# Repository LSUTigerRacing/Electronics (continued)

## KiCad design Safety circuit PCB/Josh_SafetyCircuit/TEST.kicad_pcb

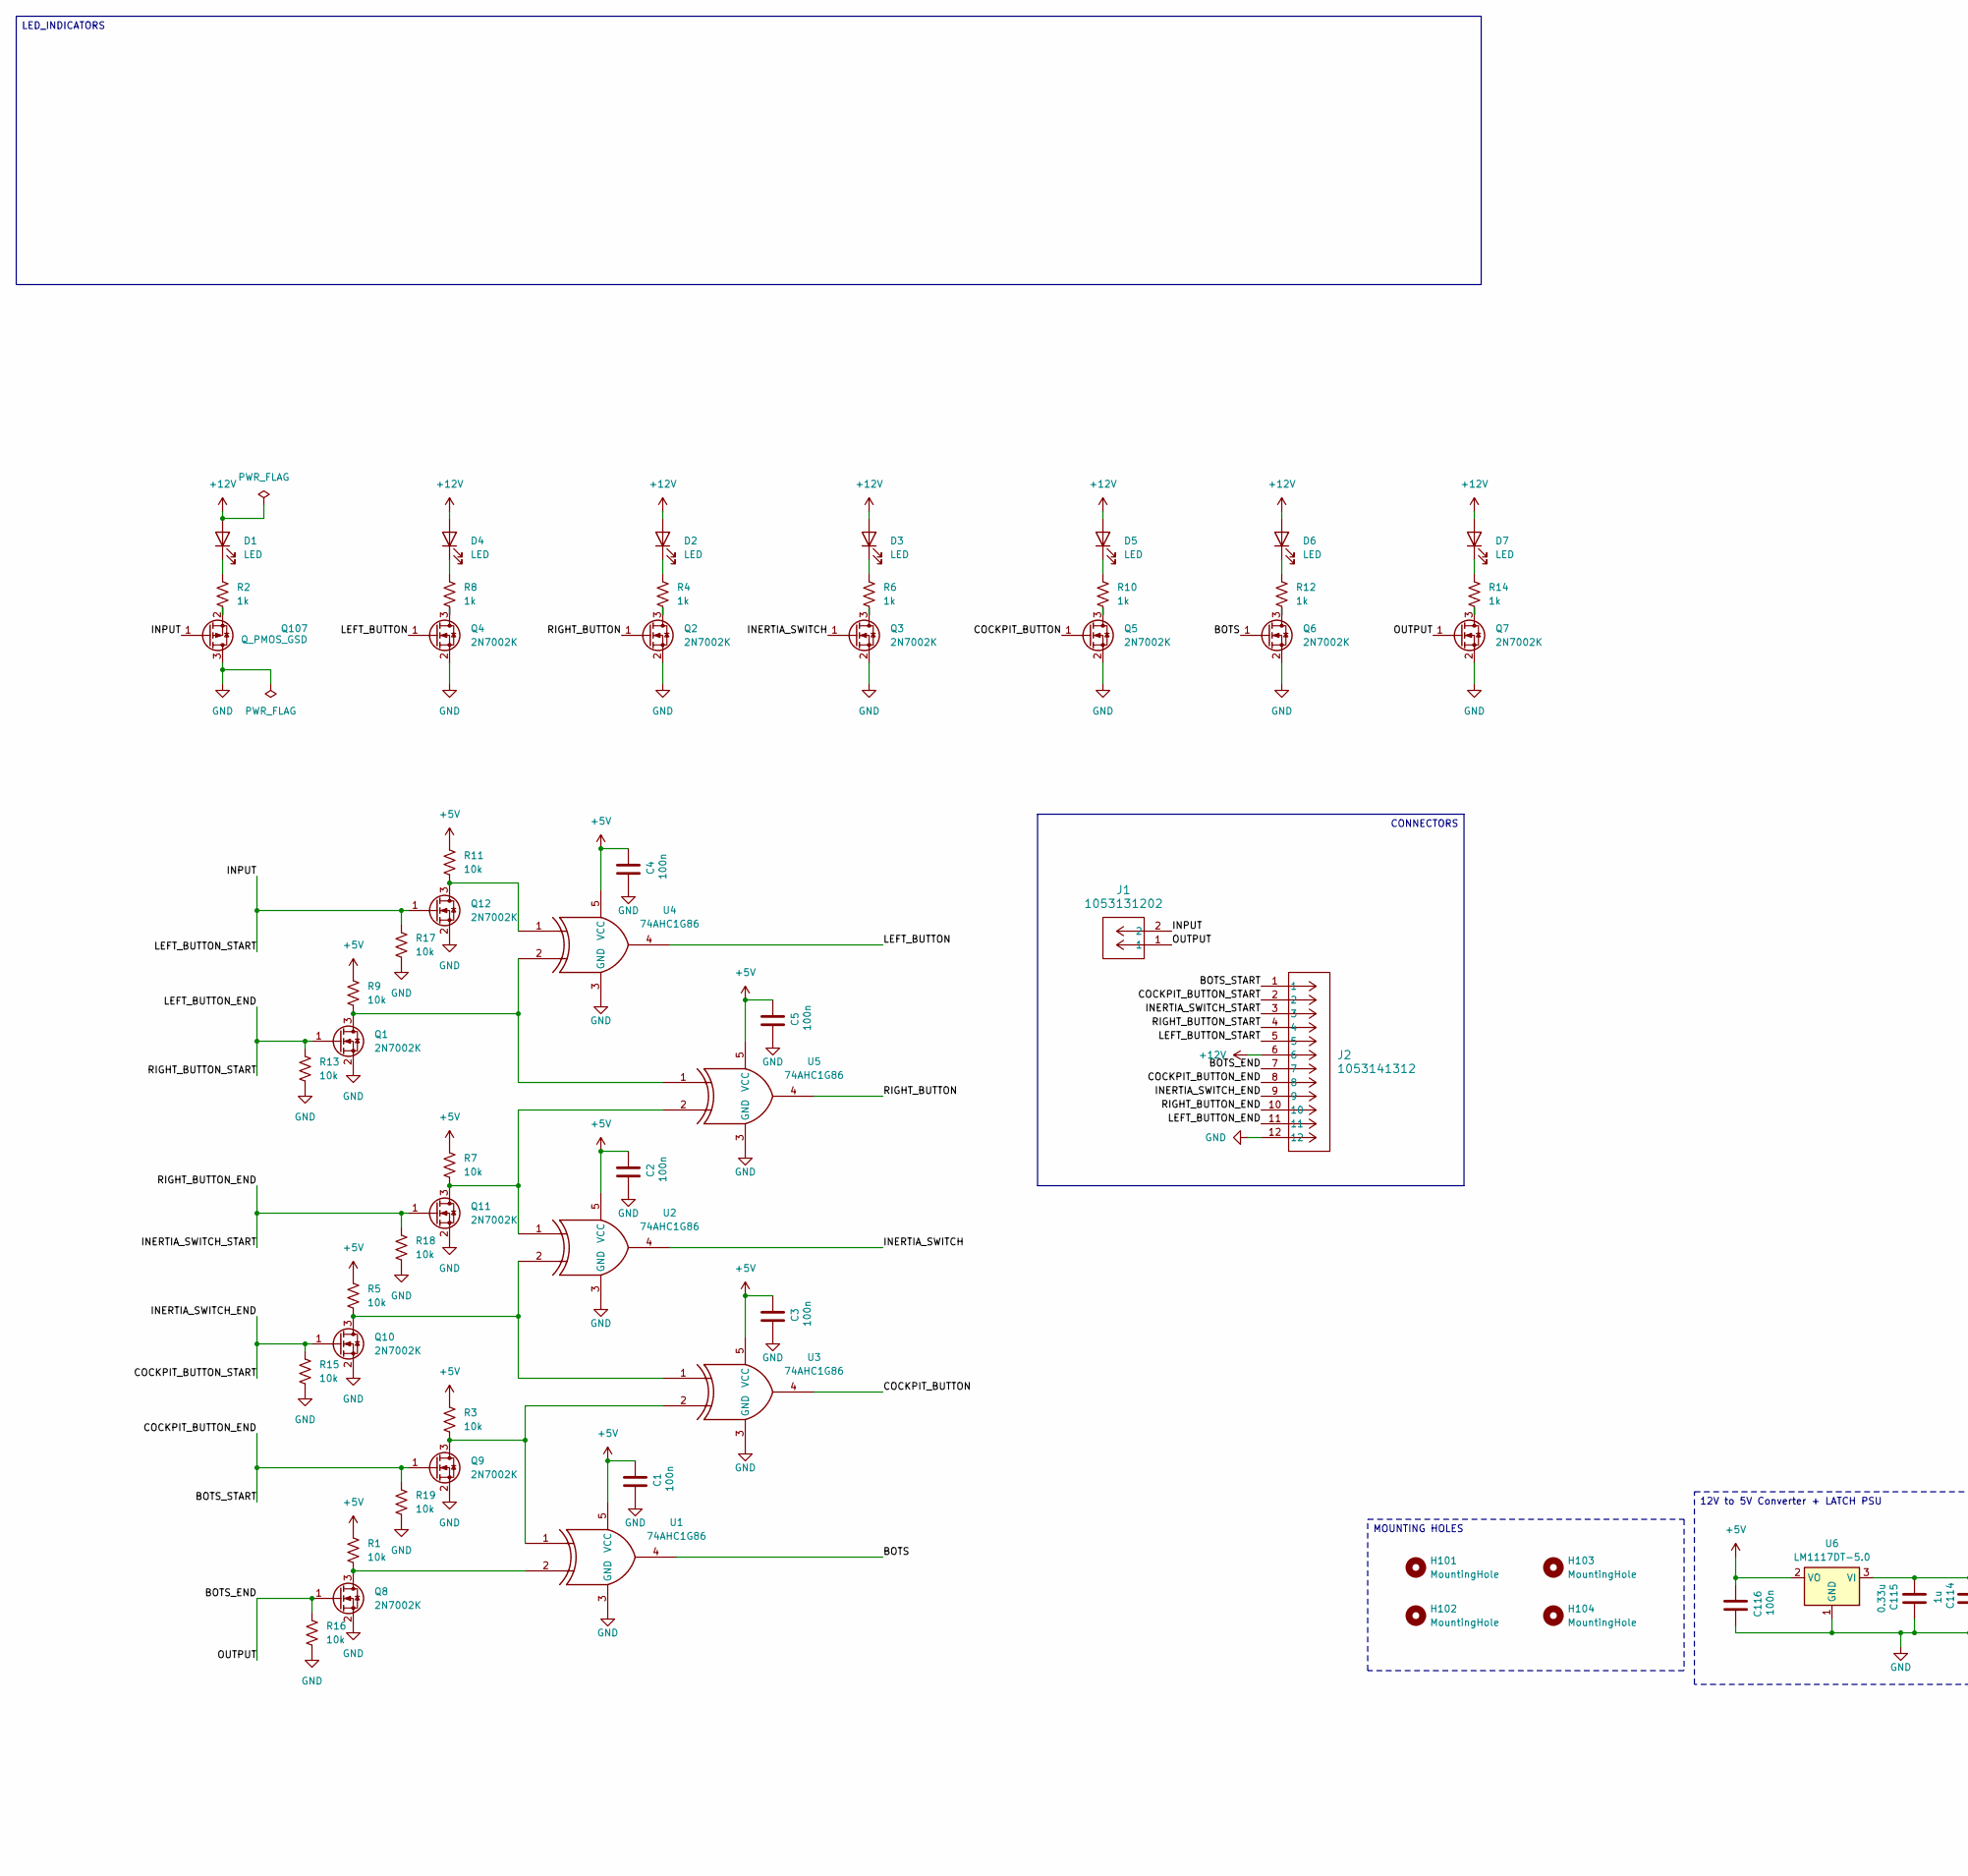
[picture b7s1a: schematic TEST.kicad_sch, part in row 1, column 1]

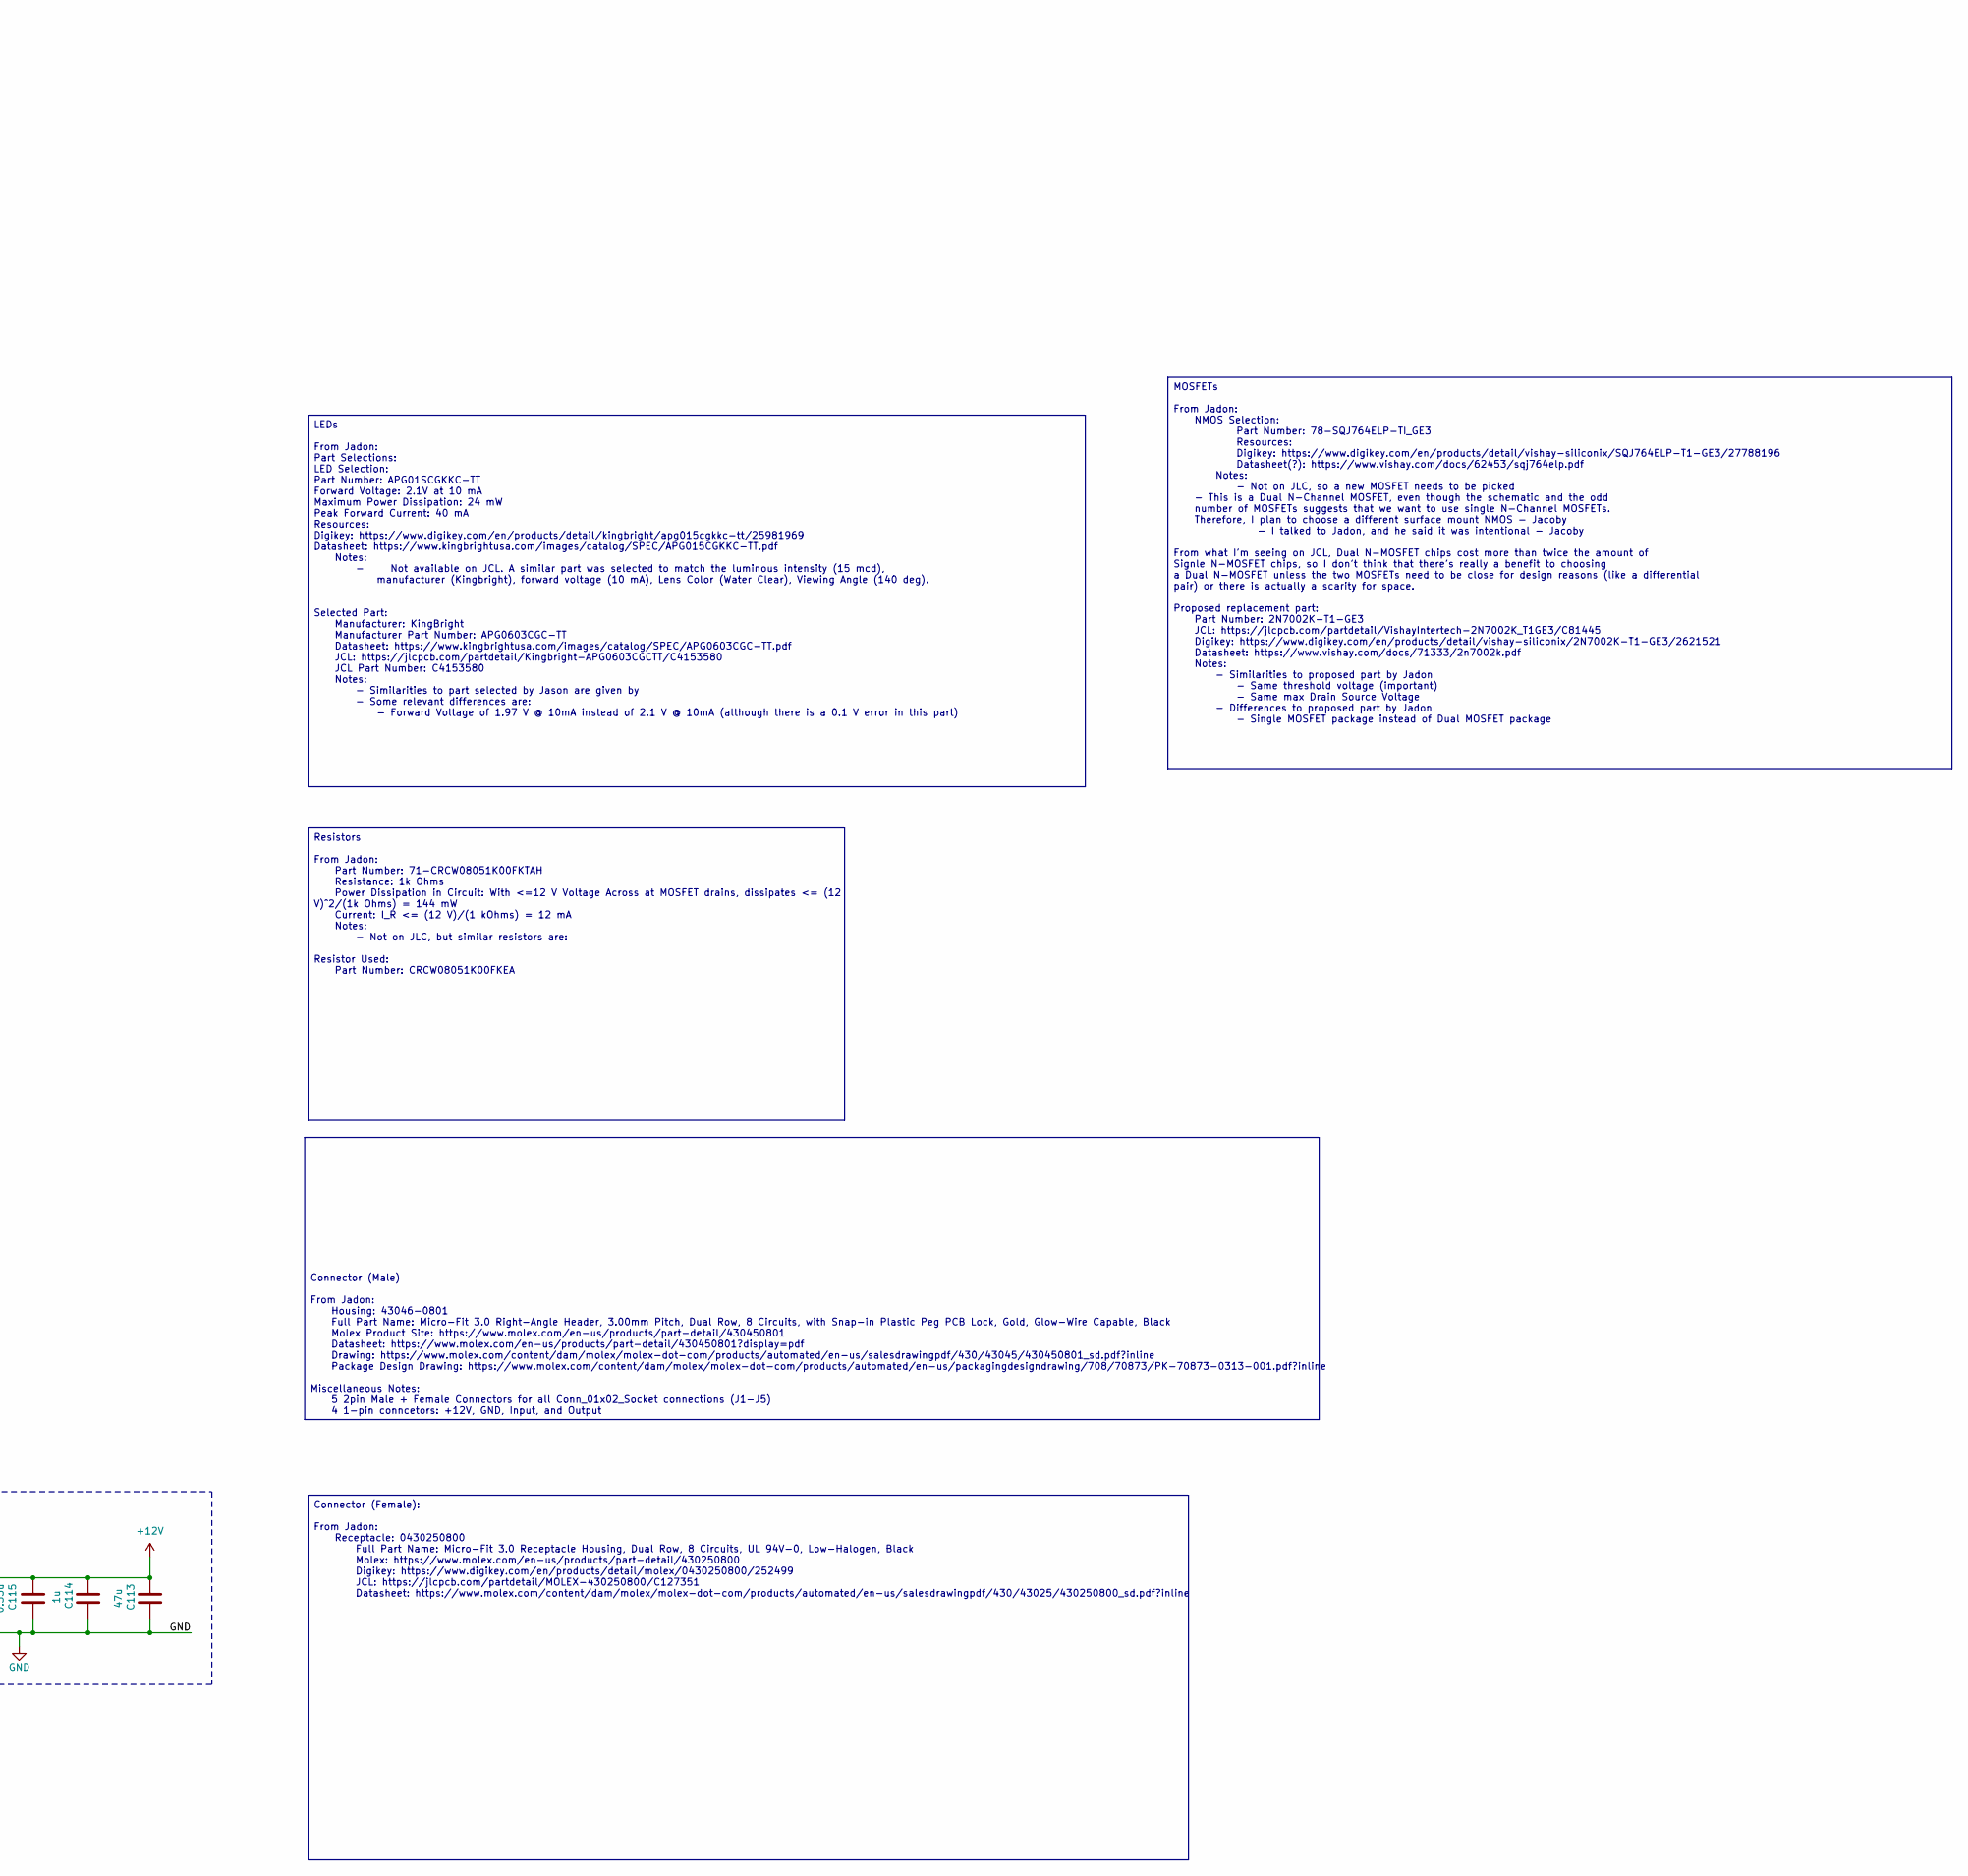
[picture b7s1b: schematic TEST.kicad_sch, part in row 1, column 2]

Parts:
C1, C2, C3, C4, C5, C116: 100n; C_0603_1608Metric_Pad1.08x0.95mm_HandSolder; JLC# C1591
C113: 47u; CP_Elec_6.3x5.4; JLC# C2836440
C114: 1u; C_0805_2012Metric_Pad1.18x1.45mm_HandSolder; JLC# C91186
C115: 0.33u; C_0603_1608Metric_Pad1.08x0.95mm_HandSolder; JLC# C282682
D1, D2, D3, D4, D5, D6, D7: LED; HL-PSC-1608U52GC-G4; MFR Part # PSC-1608U50GC-G4; JLC Part # C22371297
H101, H102, H103, H104: MountingHole; MountingHole_4.3mm_M4_DIN965_Pad_TopOnly
J1: 1053131202; CONN_SD-105313-100_02_MOL; MFR Part # 1053131202; JLC Part # C586242
J2: 1053141312; CONN_SD-105314-100_12_MOL; MFR Part # 1053141312; JLC Part # C17318123
Q1, Q2, Q3, Q4, Q5, Q6, Q7, Q8, Q9, Q10, Q11, Q12: 2N7002K; SOT-23; MFR Part # 2N7002K-T1-GE3; JLC Part # C81445
Q107: Q_PMOS_GSD; SOT-523; JLC# C96676
R1, R3, R5, R7, R9, R11, R13, R15, R16, R17, R18, R19: 10k; CRCW0805; MFR Part # CRCW08051K00FKEA; JLC Part # C844939
R2, R4, R6, R8, R10, R12, R14: 1k; CRCW0805; MFR Part # CRCW08051K00FKEA; JLC Part # C844939
U1, U2, U3, U4, U5: 74AHC1G86; SOT-23-5_HandSoldering
U6: LM1117DT-5.0; TO-252-3_TabPin2; JLC# C354068

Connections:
+5V: C1.2, C2.2, C3.2, C4.2, C5.2, C116.2, R1.1, R3.1, R5.1, R7.1, R9.1, R11.1, U1.5 (VCC), U2.5 (VCC), U3.5 (VCC), U4.5 (VCC), U5.5 (VCC), U6.2 (VO)
+12V: C113.1, C114.1, C115.1, D1.2 (A), D2.2 (A), D3.2 (A), D4.2 (A), D5.2 (A), D6.2 (A), D7.2 (A), J2.6, U6.3 (VI)
/BOTS: Q6.1 (G), U1.4
/BOTS_END: J1.1, J2.7, Q7.1 (G), Q8.1 (G), R16.1
/BOTS_START: J2.1, J2.8, Q9.1 (G), R19.1
/COCKPIT_BUTTON: Q5.1 (G), U3.4
/COCKPIT_BUTTON_START: J2.2, J2.9, Q10.1 (G), R15.1
/INERTIA_SWITCH: Q3.1 (G), U2.4
/INERTIA_SWITCH_START: J2.3, J2.10, Q11.1 (G), R18.1
/INPUT: J1.2, J2.5, Q12.1 (G), Q107.1 (G), R17.1
/LEFT_BUTTON: Q4.1 (G), U4.4
/LEFT_BUTTON_END: J2.4, J2.11, Q1.1 (G), R13.1
/RIGHT_BUTTON: Q2.1 (G), U5.4
GND: C1.1, C2.1, C3.1, C4.1, C5.1, C113.2, C114.2, C115.2, C116.1, J2.12, Q1.2 (S), Q2.2 (S), Q3.2 (S), Q4.2 (S), Q5.2 (S), Q6.2 (S), Q7.2 (S), Q8.2 (S), Q9.2 (S), Q10.2 (S), Q11.2 (S), Q12.2 (S), Q107.3 (D), R13.2, R15.2, R16.2, R17.2, R18.2, R19.2, U1.3 (GND), U2.3 (GND), U3.3 (GND), U4.3 (GND), U5.3 (GND), U6.1 (GND)
unnamed: D1.1 (K), R2.1
unnamed: D2.1 (K), R4.1
unnamed: D3.1 (K), R6.1
unnamed: D4.1 (K), R8.1
unnamed: D5.1 (K), R10.1
unnamed: D6.1 (K), R12.1
unnamed: D7.1 (K), R14.1
unnamed: Q1.3 (D), R9.2, U4.2, U5.1
unnamed: Q2.3 (D), R4.2
unnamed: Q3.3 (D), R6.2
unnamed: Q4.3 (D), R8.2
unnamed: Q5.3 (D), R10.2
unnamed: Q6.3 (D), R12.2
unnamed: Q7.3 (D), R14.2
unnamed: Q8.3 (D), R1.2, U1.2
unnamed: Q9.3 (D), R3.2, U1.1, U3.2
unnamed: Q10.3 (D), R5.2, U2.2, U3.1
unnamed: Q11.3 (D), R7.2, U2.1, U5.2
unnamed: Q12.3 (D), R11.2, U4.1
unnamed: Q107.2 (S), R2.2

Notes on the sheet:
12V to 5V Converter + LATCH PSU
MOUNTING HOLES
LEDs From Jadon: Part Selections: LED Selection: Part Number: APG01SCGKKC-TT Forward Voltage: 2.1V at 10 mA Maximum Power Dissipation: 24 mW Peak Forward Current: 40 mA Resources: Digikey: https://www.digikey.com/en/products/detail/kingbright/apg015cgkkc-tt/25981969 Datasheet: https://www.kingbrigh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
CONNECTORS
Connector (Male) From Jadon: Housing: 43046-0801 Full Part Name: Micro-Fit 3.0 Right-Angle Header, 3.00mm Pitch, Dual Row, 8 Circuits, with Snap-in Plastic Peg PCB Lock, Gold, Glow-Wire Capable, Black Molex Product Site: https://www.molex.com/en-us/products/part-detail/430450801 Datasheet: https://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
Connector (Female): From Jadon: Receptacle: 0430250800 Full Part Name: Micro-Fit 3.0 Receptacle Housing, Dual Row, 8 Circuits, UL 94V-0, Low-Halogen, Black Molex: https://www.molex.com/en-us/products/part-detail/430250800 Digikey: https://www.digikey.com/en/products/detail/molex/0430250800/252499 J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
LED_INDICATORS
Resistors From Jadon: Part Number: 71-CRCW08051K00FKTAH Resistance: 1k Ohms Power Dissipation in Circuit: With <=12 V Voltage Across at MOSFET drains, dissipates <= (12 V)^2/(1k Ohms) = 144 mW Current: I_R <= (12 V)/(1 kOhms) = 12 mA Notes: - Not on JLC, but similar resistors are: Resistor Used: Pa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
MOSFETs From Jadon: NMOS Selection: Part Number: 78-SQJ764ELP-TI_GE3 Resources: Digikey: https://www.digikey.com/en/products/detail/vishay-siliconix/SQJ764ELP-T1-GE3/27788196 Datasheet(?): https://www.vishay.com/docs/62453/sqj764elp.pdf Notes: - Not on JLC, so a new MOSFET needs to be picked - This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

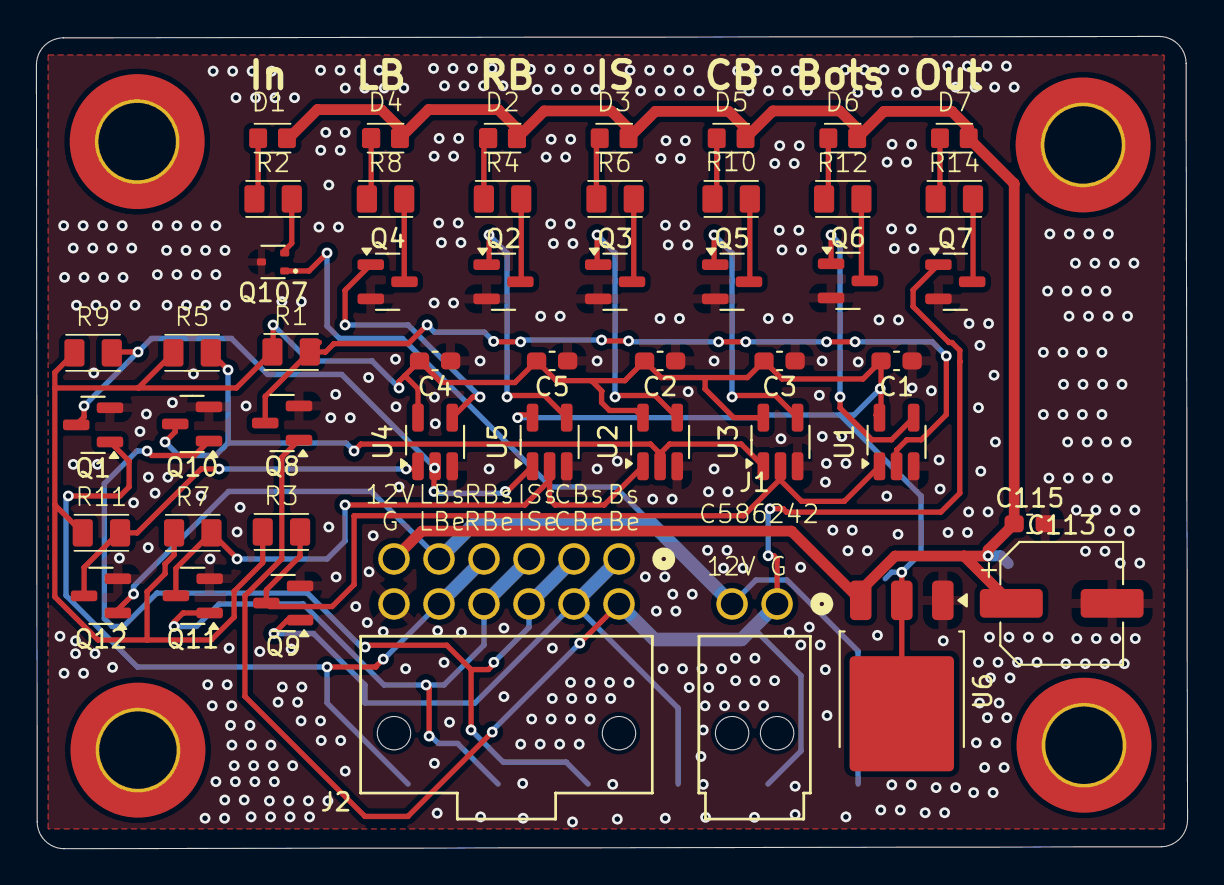
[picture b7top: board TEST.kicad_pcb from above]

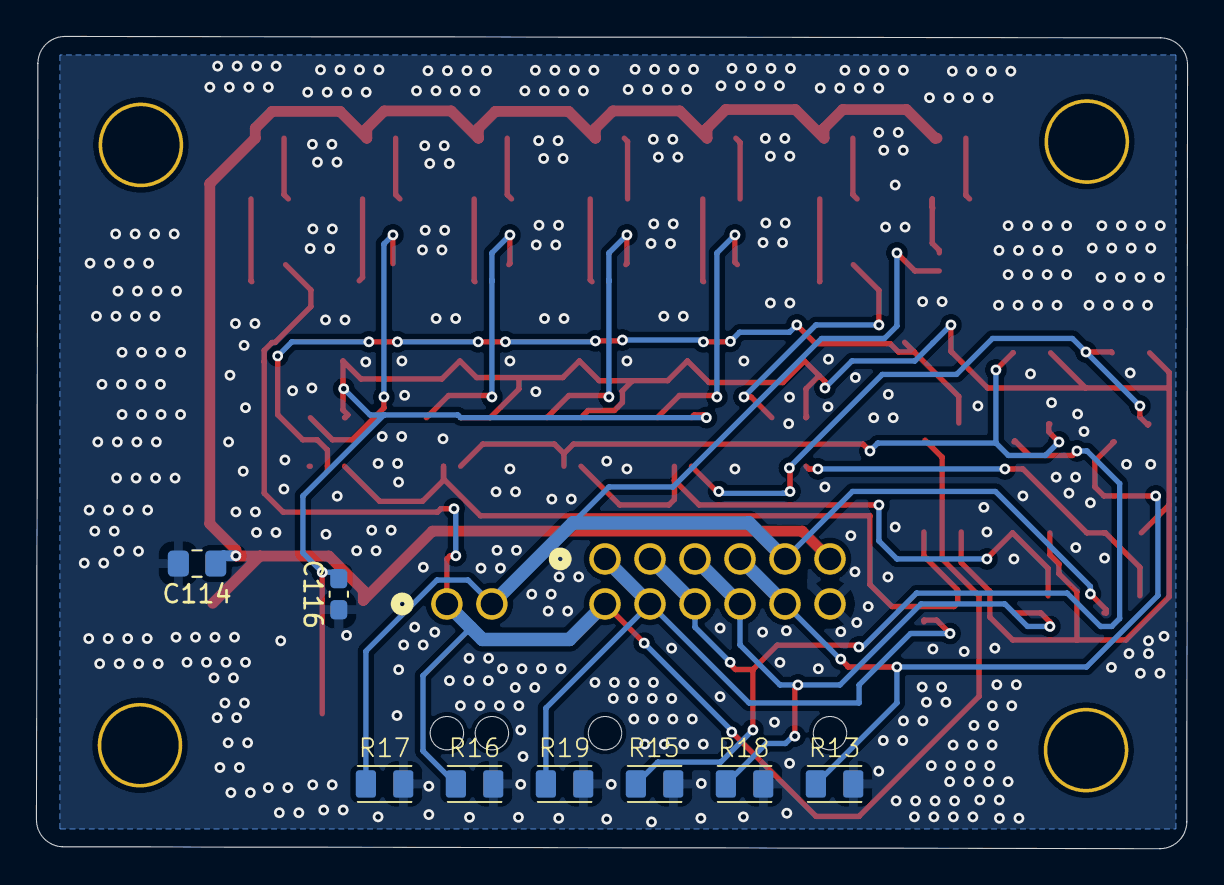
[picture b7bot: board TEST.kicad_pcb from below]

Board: 2 copper layers, 63.9 x 45.1 mm, 60 parts (8 on the bottom side), 34 nets.

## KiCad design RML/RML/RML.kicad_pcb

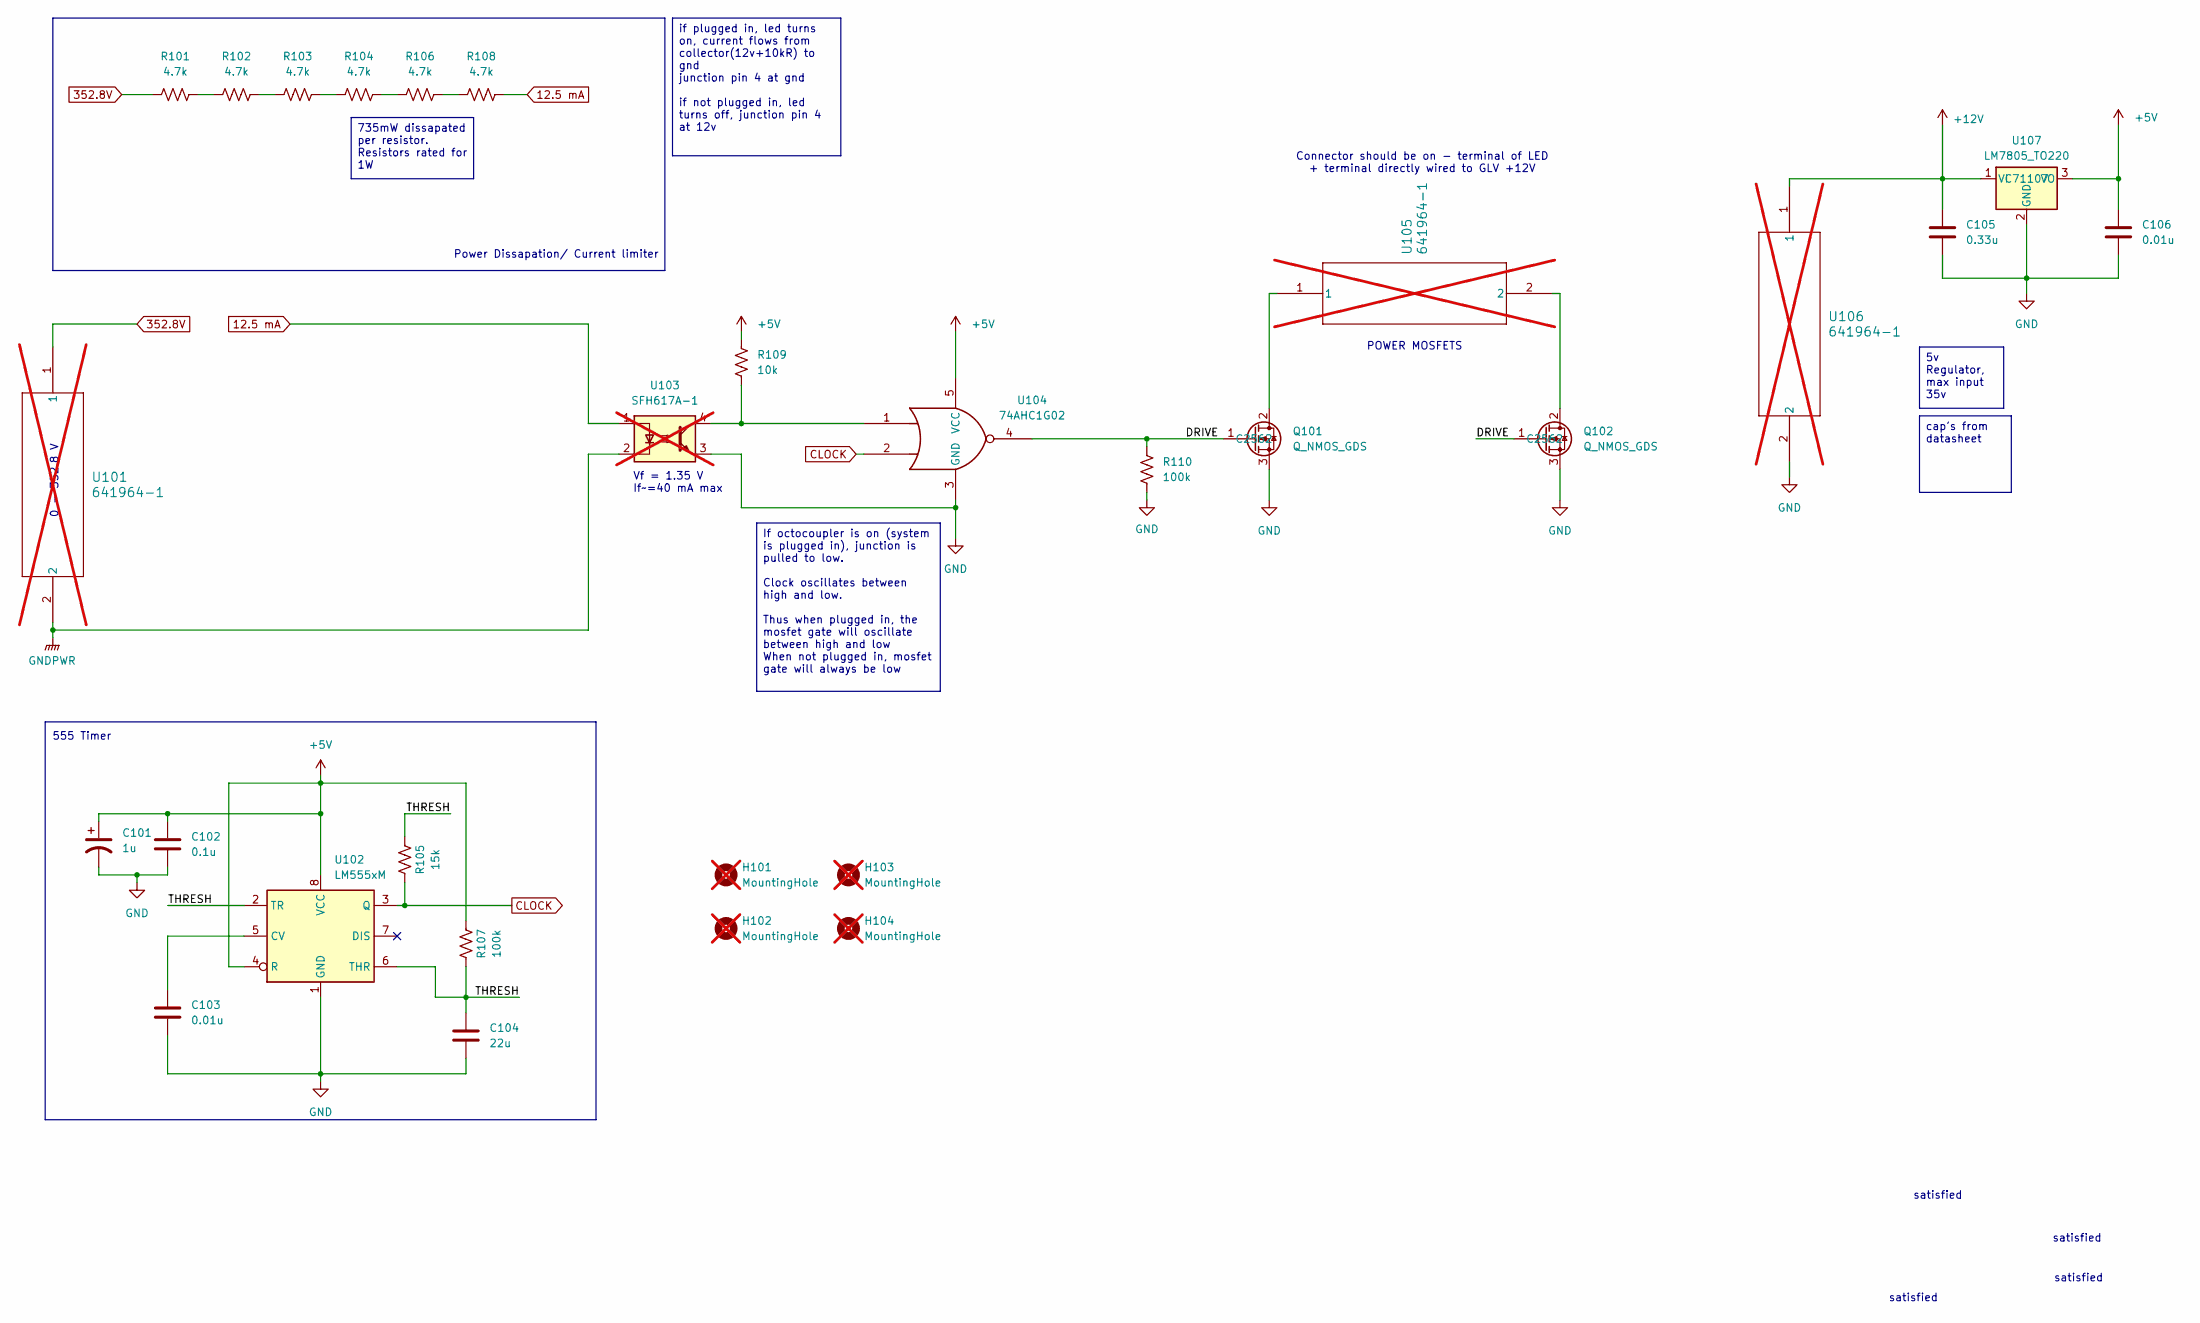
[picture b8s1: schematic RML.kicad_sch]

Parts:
C101: 1u; C_0603_1608Metric; JLC# C59782
C102: 0.1u; C_0402_1005Metric; JLC# C133086
C103, C106: 0.01u; C_0402_1005Metric; JLC# C15195
C104: 22u; C_0402_1005Metric; JLC# C105226
C105: 0.33u; C_0402_1005Metric; JLC# C107013
H101, H102, H103, H104: MountingHole; MountingHole_3.2mm_M3; not fitted
Q101, Q102: Q_NMOS_GDS; TO-220-3_Vertical; JLC# C2562
R101, R102, R103, R104, R106, R108: 4.7k; R_2512_6332Metric_Pad1.40x3.35mm_HandSolder; JLC# C163339
R105: 15k; C_0402_1005Metric; JLC# C25756
R107, R110: 100k; C_0402_1005Metric; JLC# C102750
R109: 10k; C_0402_1005Metric; JLC# C102759
U101, U105, U106: 641964-1; 641964-1_TYC; not fitted
U102: LM555xM; SOIC-8_3.9x4.9mm_P1.27mm; JLC# C90760
U103: SFH617A-1; DIP-4_W7.62mm; not fitted
U104: 74AHC1G02; SOT-23-5; JLC# C7463
U107: LM7805_TO220; TO-220-3_Vertical; JLC# C71107

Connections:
12.5 mA: R108.1, U103.1
352.8V: R101.2, U101.1
+5V: C101.1, C102.1, C106.1, R107.2, R109.1, U102.4 (R), U102.8 (VCC), U104.5 (VCC), U107.3 (VO)
+12V: C105.1, U106.1, U107.1 (VI)
/DRIVE: Q101.1 (G), Q102.1 (G), R110.2, U104.4
/THRESH: C104.2, R105.2, R107.1, U102.2 (TR), U102.6 (THR)
CLOCK: R105.1, U102.3 (Q), U104.2
GND: C101.2, C102.2, C103.2, C104.1, C105.2, C106.2, Q101.3 (S), Q102.3 (S), R110.1, U102.1 (GND), U103.3, U104.3 (GND), U106.2, U107.2 (GND)
GNDPWR: U101.2, U103.2
unnamed: Q101.2 (D), U105.1
unnamed: Q102.2 (D), U105.2
unnamed: R101.1, R102.2
unnamed: R102.1, R103.2
unnamed: R103.1, R104.2
unnamed: R104.1, R106.2
unnamed: R106.1, R108.2
unnamed: R109.2, U103.4, U104.1
unnamed: C103.1, U102.5 (CV)

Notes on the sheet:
555 Timer
POWER MOSFETS
Connector should be on - terminal of LED + terminal directly wired to GLV +12V
0 - 352.8 V
satisfied
Vf = 1.35 V If~=40 mA max
Power Dissapation/ Current limiter
if plugged in, led turns on, current flows from collector(12v+10kR) to gnd junction pin 4 at gnd if not plugged in, led turns off, junction pin 4 at 12v
cap's from datasheet
5v Regulator, max input 35v
735mW dissapated per resistor. Resistors rated for 1W
If octocoupler is on (system is plugged in), junction is pulled to low. Clock oscillates between high and low. Thus when plugged in, the mosfet gate will oscillate between high and low When not plugged in, mosfet gate will always be low

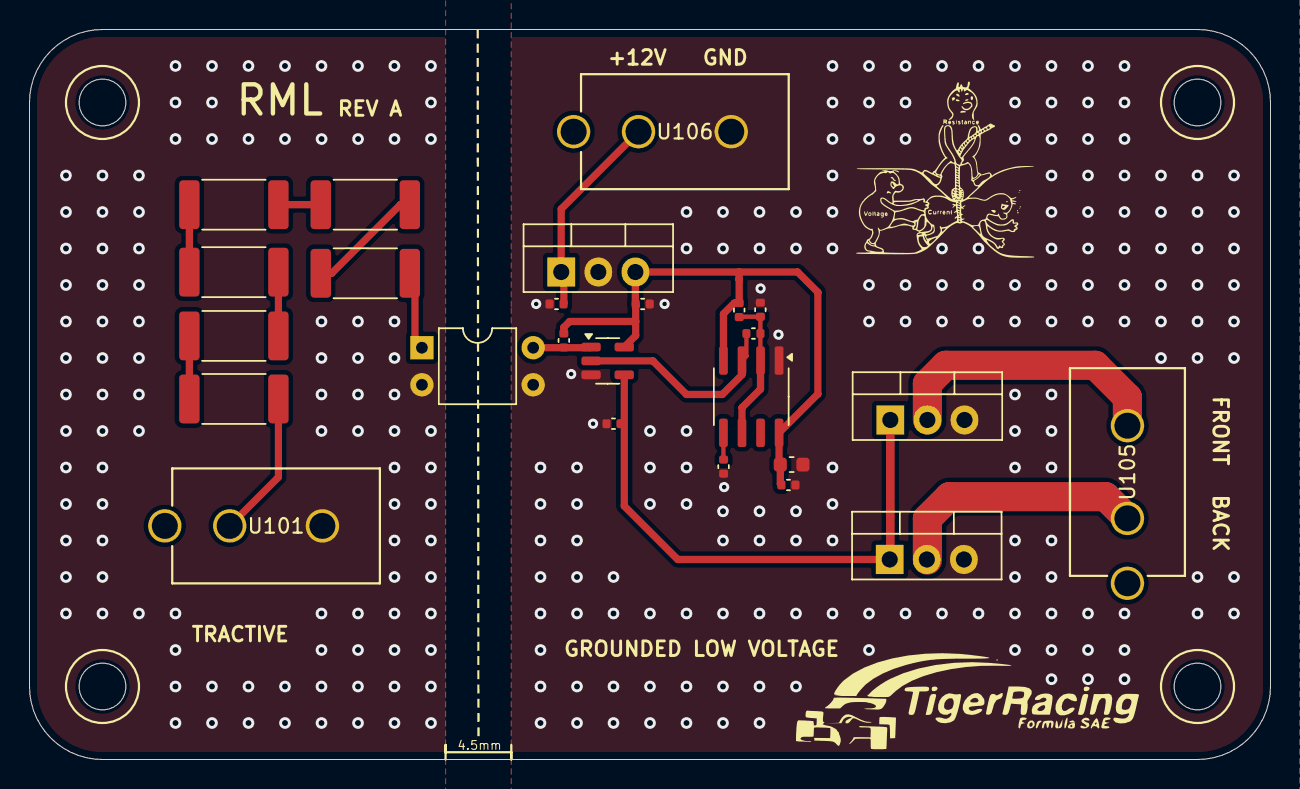
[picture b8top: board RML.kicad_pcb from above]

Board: 4 copper layers, 85.0 x 50.0 mm, 29 parts (0 on the bottom side), 18 nets.

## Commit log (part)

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2025-09-22 BSPD Stuff
2025-11-01 finished schematic and layout
2026-01-15 Spring Semester V2 Fault Latch
2026-03-17 changes mounting holes on discharge to M4
    gareth wants all pcb mounting holes to M4
2026-03-18 Almost finished Fault Latch Layout Spring Semester V2.0
2026-03-18 Discharge
    Added through hole mosfets and LED driver to DIscharge board
2026-03-18 Bom + Schematic Redone V3.2
2026-03-25 vcu kicad filrd
2026-03-27 added power board
2026-03-27 enhance (README): update README
2026-03-30 discharge fixed
    added zener diode from nmos gate to source, also added indiactor LED
2026-03-31 Charging PCB 12V+ wire length increased
2026-03-31 Fault Latch Finished Schematic V4
    Finished revised schematic and started on layout.
2026-04-02 Fault Latch V4 (almost RTO needs mounting holes)
    Needs a final edge cut and mounting holes placed on it, besides that everything else is ready.
2026-04-02 Fault Latch RTO V4
    Ready to order might push a different one with more sketches for final order.
2026-04-02 Minor Ground Revision FL V4
2026-04-02 Final RTO Fault Latch V4
2026-04-05 IR holder board
2026-04-06 FINAL RTO FL V4
    Added tables for I/O and fixed some traces
2026-04-23 charging holes
    added M4 holes to charging
2026-04-24 Added modal for Prechg, FL
    Look in PCBMOdal26 file and open respective workbench files for precharge and FL, figure it out
2026-04-29 Fixed Discharge + Added RML Quick files
2026-05-16 Fixed up the Git a bit + added RML Quick and RML LED Driver
2026-05-16 Added up to date BSPD back to git bc yianni is a bum
2026-06-02 Added Remade RML and Safety Circuit
2026-06-02 Fixed Small Comparator issue on RML Switiching
2026-06-15 precharge code
    removed delay on precharge teensy
